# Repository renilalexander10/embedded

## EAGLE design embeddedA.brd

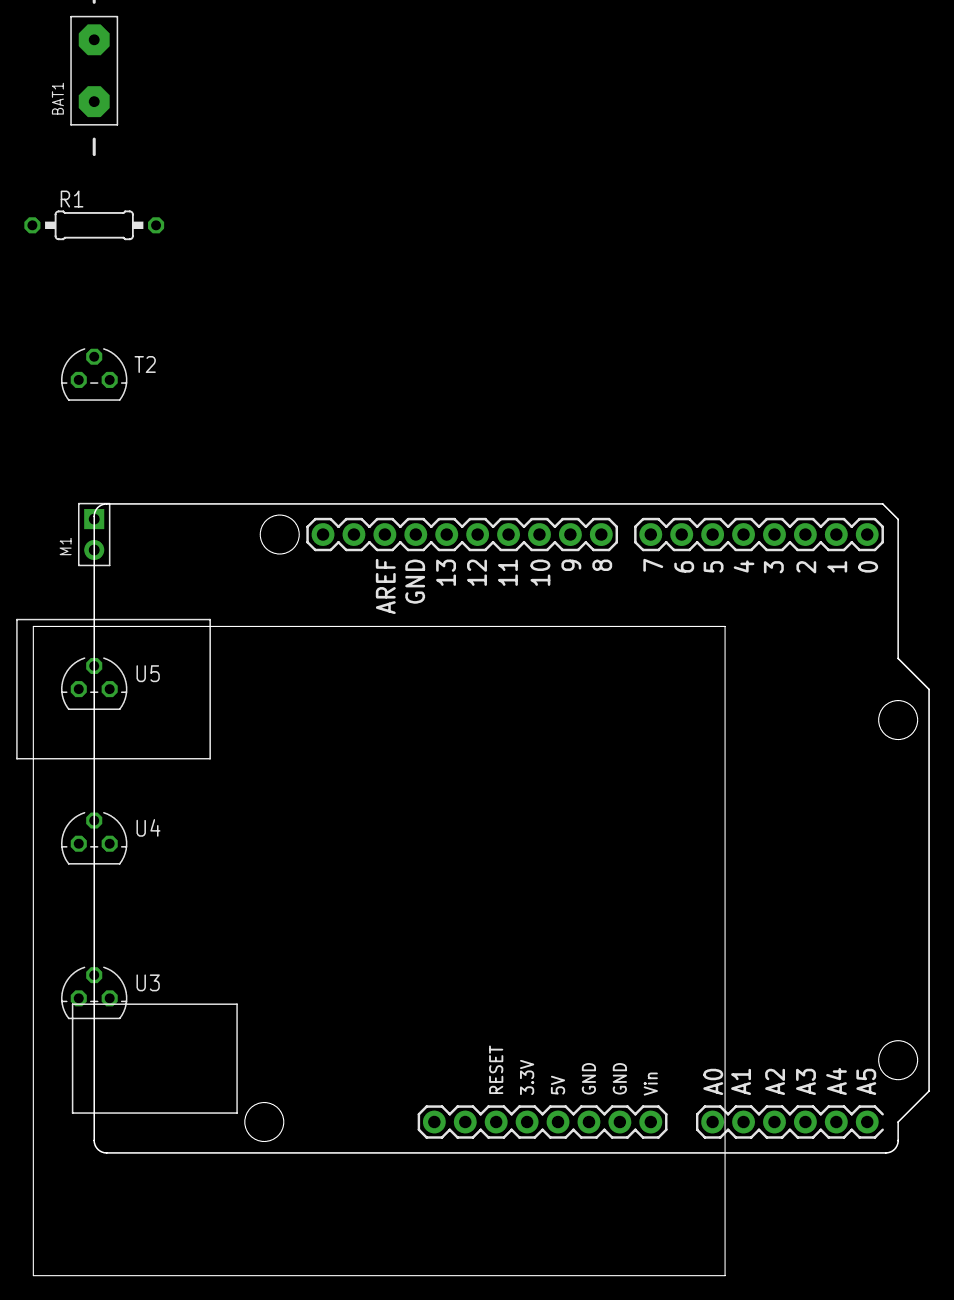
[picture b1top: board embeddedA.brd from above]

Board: 2 copper layers, 73.6 x 63.4 mm, 8 parts (0 on the bottom side), 9 nets, no tracks yet.

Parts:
BAT1: DC-POWER
M1: 2P-2.54-65/35MIL
R1: 330‎Ω; 0207/10
T2: TO92
U2: ARDUINO_UNO
U3, U4, U5: TO92

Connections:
unnamed: U3.3, U4.3, U5.3
unnamed: U3.1, U4.1, U5.1
unnamed: U2.A0, U3.2
unnamed: U2.A1, U4.2
unnamed: U2.A2, U5.2
unnamed: T2.2, U2.7
unnamed: M1.2, R1.1
unnamed: R1.2, T2.3
unnamed: BAT1.+, T2.1
